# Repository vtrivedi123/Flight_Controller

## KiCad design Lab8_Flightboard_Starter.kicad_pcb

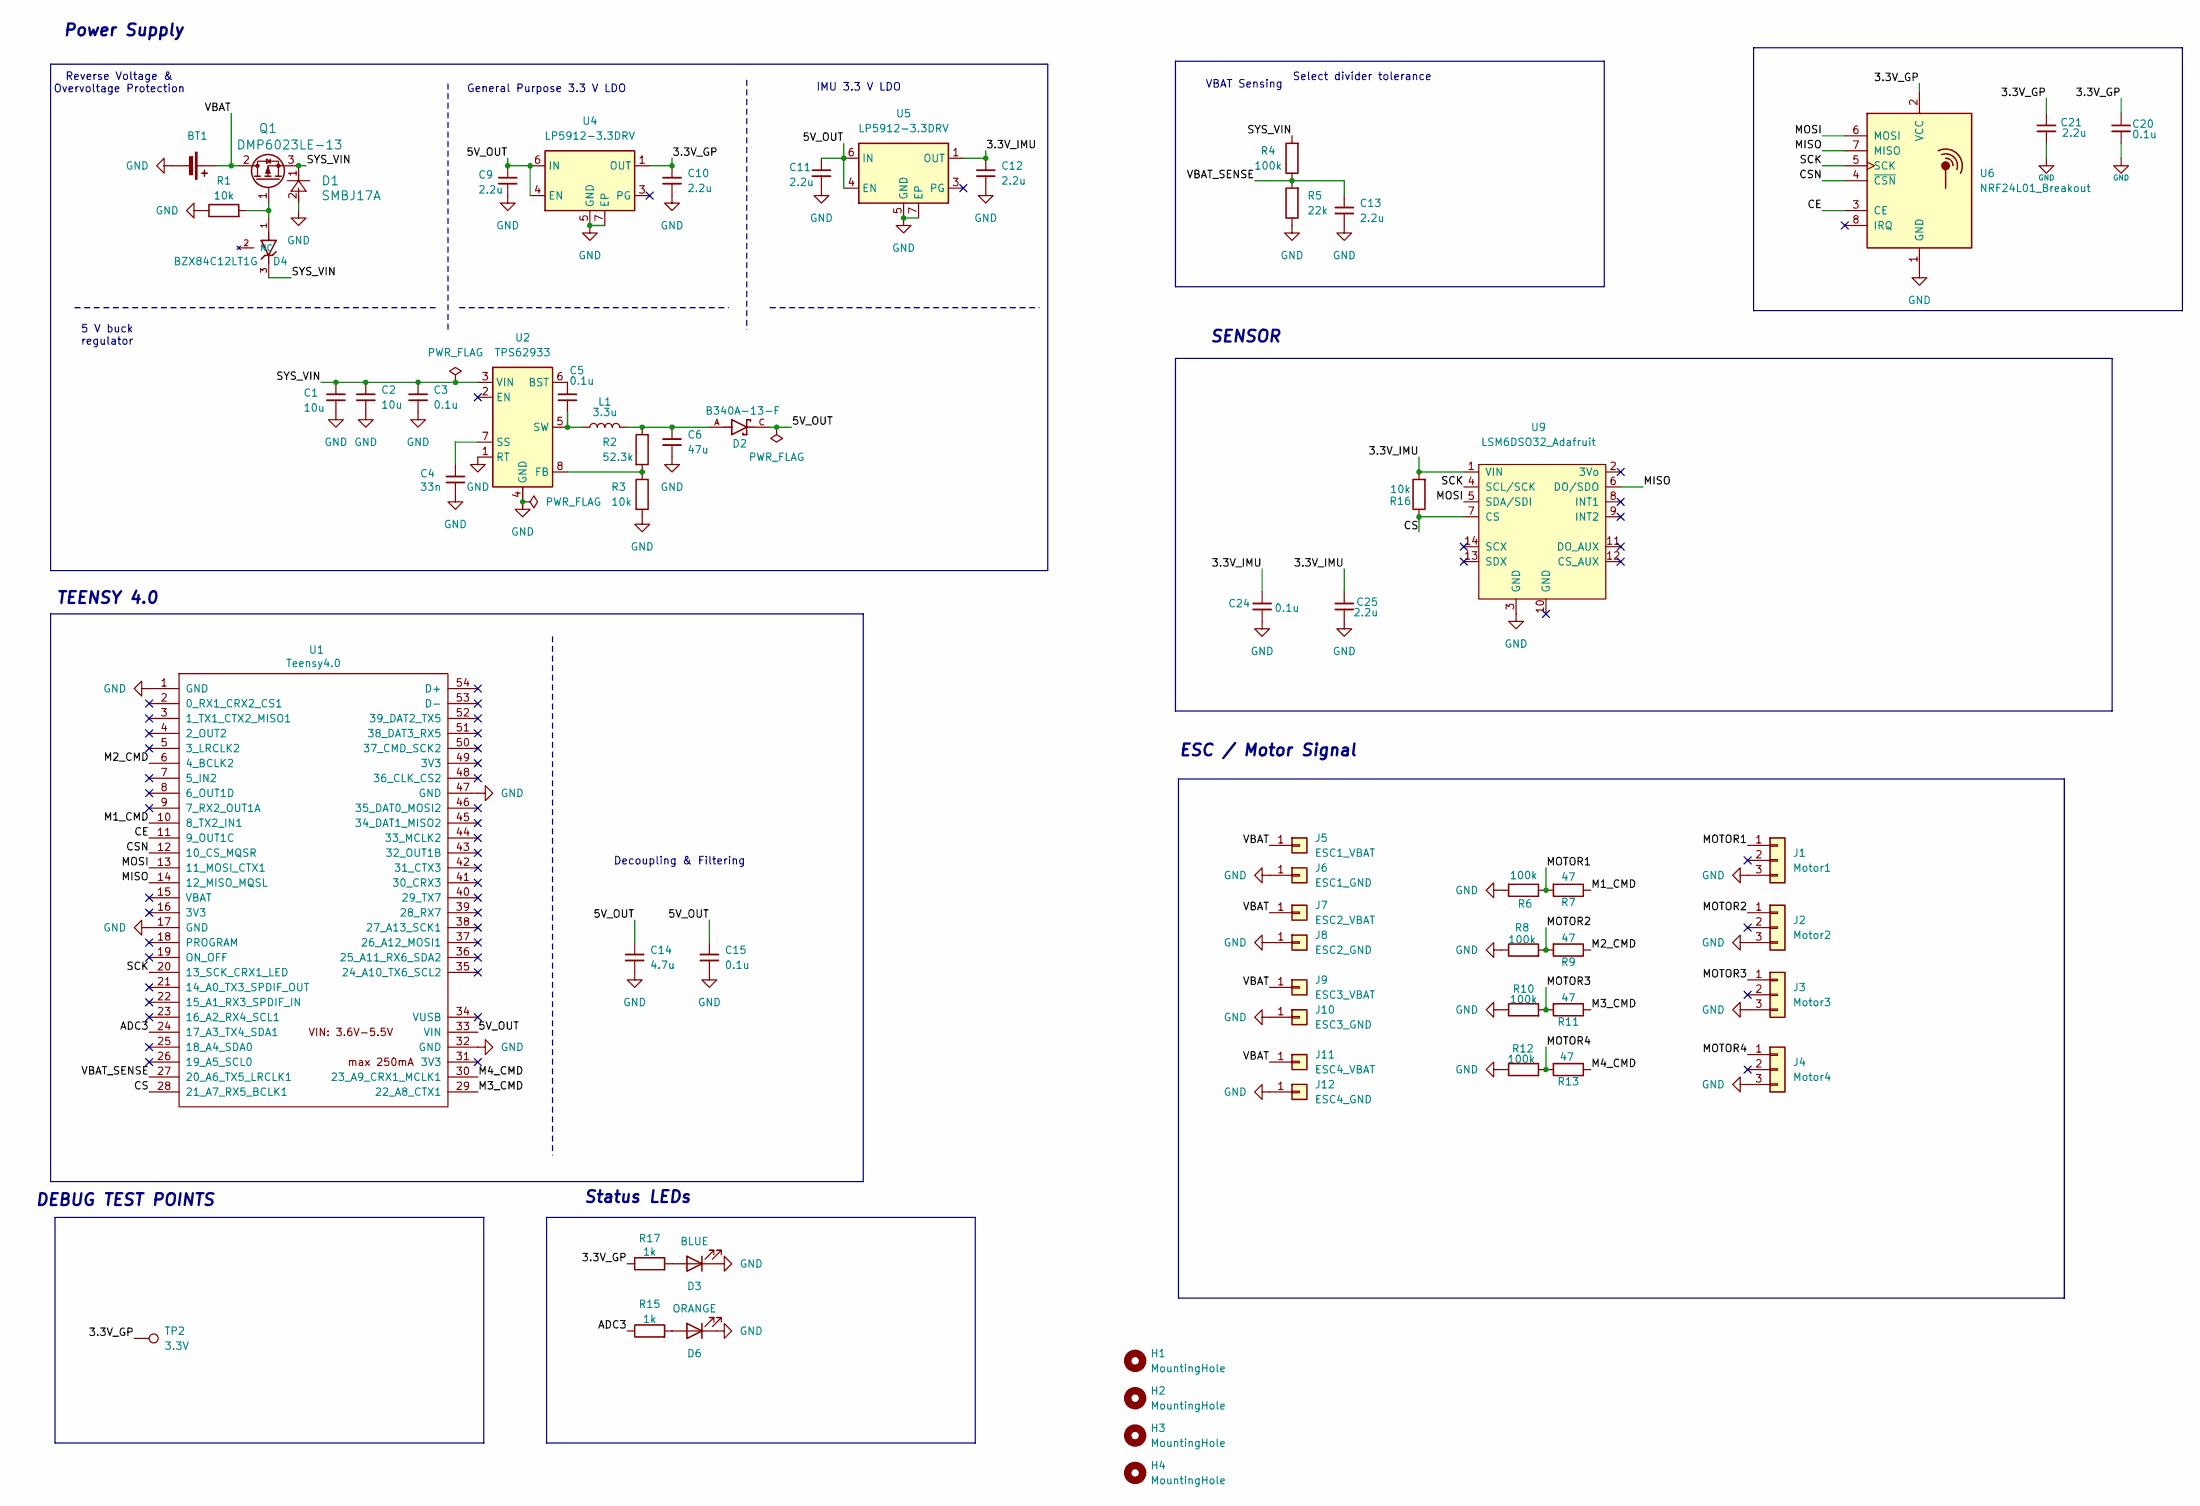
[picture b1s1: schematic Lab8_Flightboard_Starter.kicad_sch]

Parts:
BT1: 3S_LiPo; Pad_x2
C1, C2: 10u; C_1206_3216Metric_Pad1.33x1.80mm_HandSolder
C3, C5, C15, C20, C24: 0.1u; C_0805_2012Metric_Pad1.18x1.45mm_HandSolder
C4: 33n; C_0805_2012Metric_Pad1.18x1.45mm_HandSolder
C6: 47u; C_1206_3216Metric_Pad1.33x1.80mm_HandSolder
C9, C10, C11, C12, C13, C21, C25: 2.2u; C_0805_2012Metric_Pad1.18x1.45mm_HandSolder
C14: 4.7u; C_0805_2012Metric_Pad1.18x1.45mm_HandSolder
D1: SMBJ17A; SMBJSeries_LTF
D2: B340A-13-F; DIOM5226X240N; PARTREV 17-2
D3: BLUE; LED_0805_2012Metric_Pad1.15x1.40mm_HandSolder
D4: BZX84C12LT1G; SOT95P240X111-3N; PARTREV 23
D6: ORANGE; LED_0805_2012Metric_Pad1.15x1.40mm_HandSolder
H1, H2, H3, H4: MountingHole; MountingHole_3.3mm_no-courtyard
J1: Motor1; PinHeader_1x03_P2.54mm_Vertical
J2: Motor2; PinHeader_1x03_P2.54mm_Vertical
J3: Motor3; PinHeader_1x03_P2.54mm_Vertical
J4: Motor4; PinHeader_1x03_P2.54mm_Vertical
J5: ESC1_VBAT; Pad_x1_6mm
J6: ESC1_GND; Pad_x1_6mm
J7: ESC2_VBAT; Pad_x1_6mm
J8: ESC2_GND; Pad_x1_6mm
J9: ESC3_VBAT; Pad_x1_6mm
J10: ESC3_GND; Pad_x1_6mm
J11: ESC4_VBAT; Pad_x1_6mm
J12: ESC4_GND; Pad_x1_6mm
L1: 3.3u; IND_SRP7028A-4R7M_BRN
Q1: DMP6023LE-13; DMP6023LE-13_Official
R1, R3, R16: 10k; R_0805_2012Metric_Pad1.20x1.40mm_HandSolder
R2: 52.3k; R_0805_2012Metric_Pad1.20x1.40mm_HandSolder
R4, R6, R8, R10, R12: 100k; R_0805_2012Metric_Pad1.20x1.40mm_HandSolder
R5: 22k; R_0805_2012Metric_Pad1.20x1.40mm_HandSolder
R7, R9, R11, R13: 47; R_0805_2012Metric_Pad1.20x1.40mm_HandSolder
R15, R17: 1k; R_0805_2012Metric_Pad1.20x1.40mm_HandSolder
TP2: 3.3V; TestPoint_Pad_2.0x2.0mm
U1: Teensy4.0; Teensy40
U2: TPS62933; SOT-583-8
U4, U5: LP5912-3.3DRV; WSON-6-1EP_2x2mm_P0.65mm_EP1x1.6mm_ThermalVias
U6: NRF24L01_Breakout; nRF24L01_Breakout
U9: LSM6DSO32_Adafruit

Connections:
/3.3V_GP: C10.1, C20.1, C21.1, R17.1, TP2.1 (1_1), U4.1 (OUT), U6.2 (VCC)
/3.3V_IMU: C12.1, C24.1, C25.1, R16.2, U5.1 (OUT), U9.1 (VIN)
/5V_OUT: C9.1, C11.1, C14.1, C15.1, D2.C, U1.33 (VIN), U4.4 (EN), U4.6 (IN), U5.4 (EN), U5.6 (IN)
/ADC3: R15.1, U1.24 (17_A3_TX4_SDA1)
/CE: U1.11 (9_OUT1C), U6.3 (CE)
/CS: R16.1, U1.28 (21_A7_RX5_BCLK1), U9.7 (CS)
/CSN: U1.12 (10_CS_MQSR), U6.4 (~CSN)
/M1_CMD: R7.1, U1.10 (8_TX2_IN1)
/M2_CMD: R9.1, U1.6 (4_BCLK2)
/M3_CMD: R11.1, U1.29 (22_A8_CTX1)
/M4_CMD: R13.1, U1.30 (23_A9_CRX1_MCLK1)
/MISO: U1.14 (12_MISO_MQSL), U6.7 (MISO), U9.6 (DO/SDO)
/MOSI: U1.13 (11_MOSI_CTX1), U6.6 (MOSI), U9.5 (SDA/SDI)
/MOTOR1: J1.1, R6.1, R7.2
/MOTOR2: J2.1, R8.2, R9.2
/MOTOR3: J3.1, R10.2, R11.2
/MOTOR4: J4.1, R12.2, R13.2
/SCK: U1.20 (13_SCK_CRX1_LED), U6.5 (SCK), U9.4 (SCL/SCK)
/SYS_VIN: C1.1, C2.1, C3.1, D1.1, D4.3, Q1.3, R4.2, U2.3 (VIN)
/VBAT: BT1.1 (+), J5.1 (Pin_1_1), J7.1 (Pin_1_1), J9.1 (Pin_1_1), J11.1 (Pin_1_1), Q1.2
/VBAT_SENSE: C13.1, R4.1, R5.2, U1.27 (20_A6_TX5_LRCLK1)
GND: BT1.2 (-), C1.2, C2.2, C3.2, C4.1, C6.2, C9.2, C10.2, C11.2, C12.2, C13.2, C14.2, C15.2, C20.2, C21.2, C24.2, C25.2, D1.2, D3.1 (K), D6.1 (K), J1.3, J2.3, J3.3, J4.3, J6.1 (Pin_1_1), J8.1 (Pin_1_1), J10.1 (Pin_1_1), J12.1 (Pin_1_1), R1.1, R3.2, R5.1, R6.2, R8.1, R10.1, R12.1, U1.1 (GND), U1.17 (GND), U1.32 (GND), U1.47 (GND), U2.1 (RT), U2.4 (GND), U4.5 (GND), U4.7 (EP), U5.5 (GND), U5.7 (EP), U6.1 (GND), U9.3 (GND)
unnamed: C6.1, D2.A, L1.2, R2.1
unnamed: D3.2 (A), R17.2
unnamed: D4.1, Q1.1, R1.2
unnamed: D6.2 (A), R15.2
unnamed: C5.1, U2.6 (BST)
unnamed: R2.2, R3.1, U2.8 (FB)
unnamed: C4.2, U2.7 (SS)
unnamed: C5.2, L1.1, U2.5 (SW)

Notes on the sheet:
SENSOR
Power Supply
VBAT Sensing
5 V buck regulator
Status LEDs
IMU 3.3 V LDO
Select divider tolerance
Decoupling & Filtering
DEBUG TEST POINTS
TEENSY 4.0
ESC / Motor Signal
Reverse Voltage & Overvoltage Protection
General Purpose 3.3 V LDO

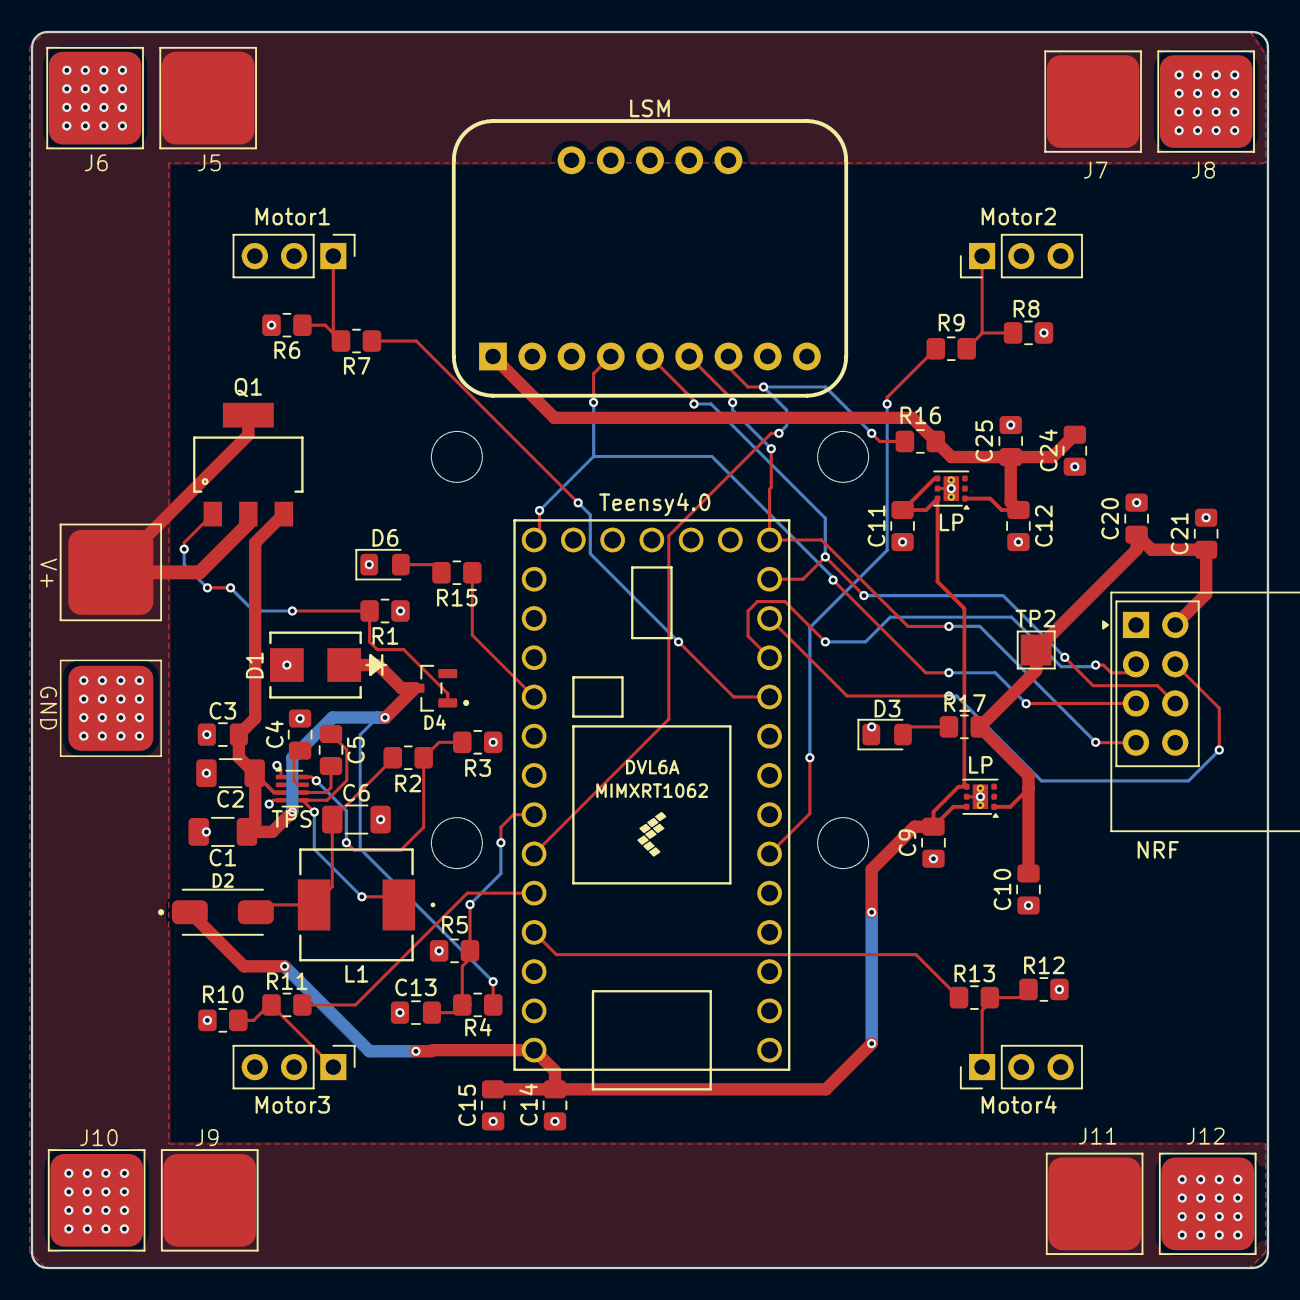
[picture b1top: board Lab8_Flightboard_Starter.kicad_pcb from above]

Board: 2 copper layers, 80.0 x 80.0 mm, 64 parts (0 on the bottom side), 30 nets.
